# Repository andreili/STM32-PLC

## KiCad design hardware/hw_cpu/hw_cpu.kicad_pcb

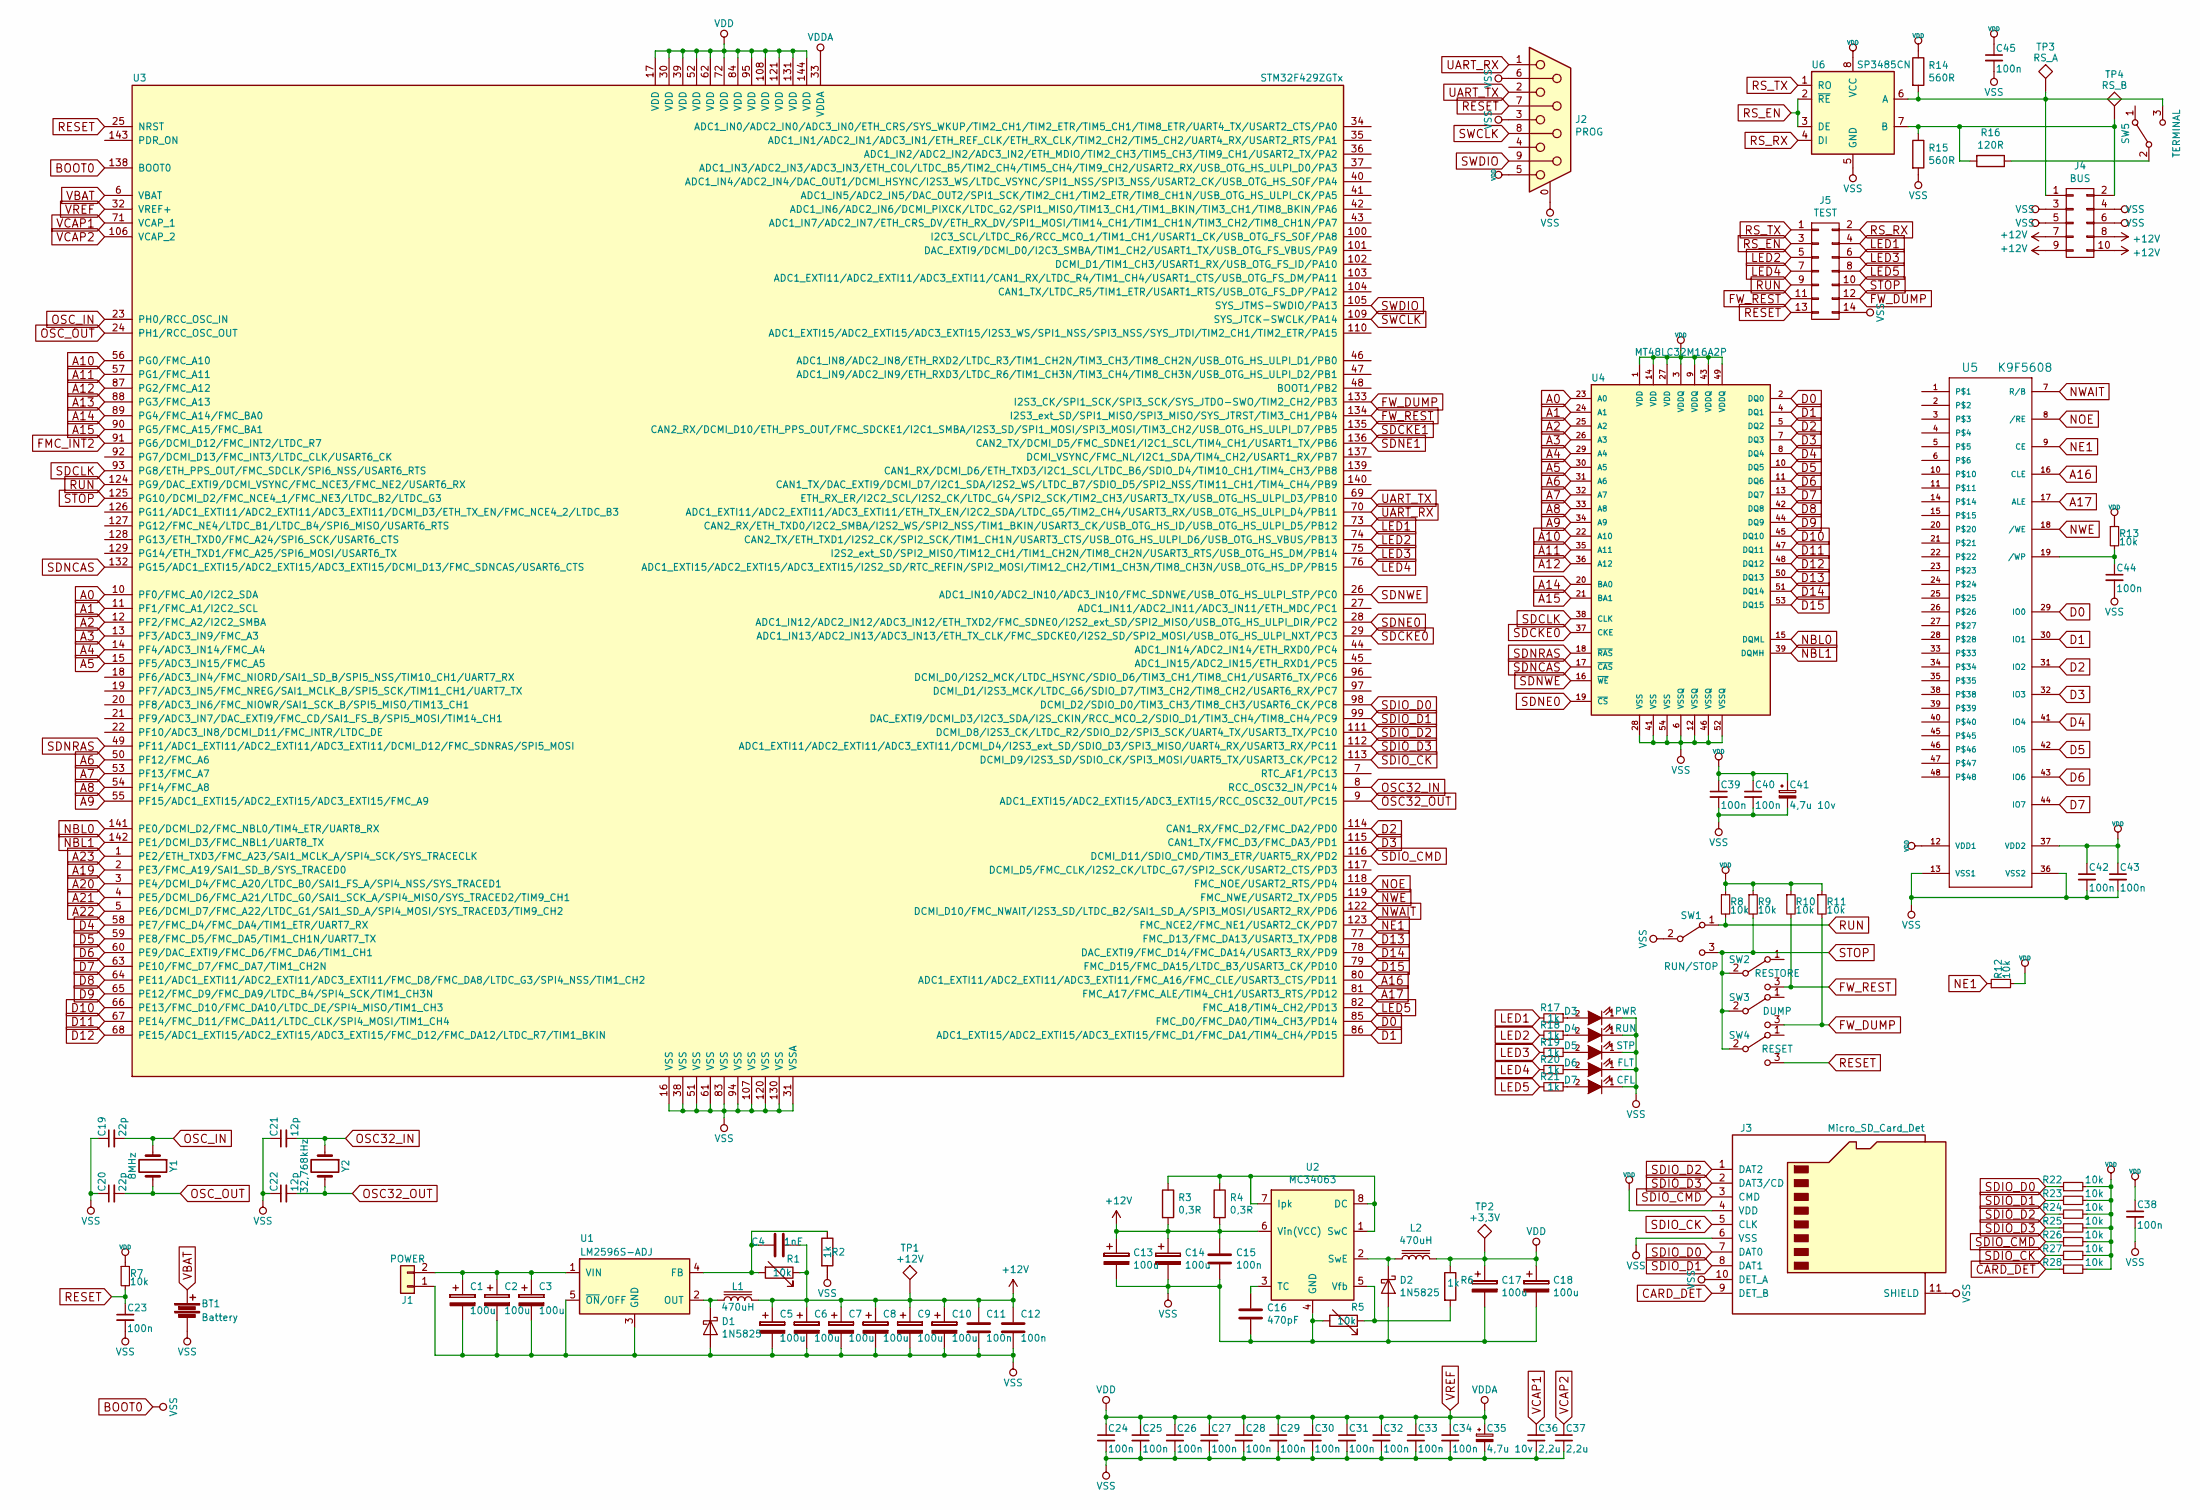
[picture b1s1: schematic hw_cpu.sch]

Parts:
BT1: Battery; keystone_107
C1, C2, C3, C5, C6, C7, C8, C9, C10, C13, C14, C17, C18: 100u; CP_Elec_8x6.5
C4: 1nF; C_0402
C11, C12, C15, C23, C24, C25, C26, C27, C28, C29, C30, C31, C32, C33, C34, C38, C39, C40, C42, C43, C44, C45: 100n; C_0805
C16: 470pF; C_0402
C19, C20: 22p; C_0402
C21, C22: 12p; C_0402
C35: 4,7u 10v; CP_Tantalum_Case-A_EIA-3216-18_Reflow
C36, C37: 2,2u; C_0402
C41: 4,7u 10v; CP_Tantalum_Case-B_EIA-3528-21_Reflow
D1, D2: 1N5825; D_SMA
D3: PWR; LED_0805
D4: RUN; LED_0805
D5: STP; LED_0805
D6: FLT; LED_0805
D7: CFL; LED_0805
J1: POWER; PhoenixContact_MC-G_02x3.81mm_Angled
J2: PROG; DB9FC
J3: Micro_SD_Card_Det; Conn_uSDcard
J4: BUS; he10-10d
J5: TEST; he10-14d
L1, L2: 470uH; Neosid_Inductor_SM-PIC1004H
R1, R5, R7, R8, R9, R10, R11, R12, R13, R22, R23, R24, R25, R26, R27, R28: 10k; R_0805
R2, R6, R17, R18, R19, R20, R21: 1k; R_0805
R3, R4: 0,3R; R_2010
R14, R15: 560R; R_0805
R16: 120R; R_0805
SW1: RUN/STOP; KSA_Tactile_SPST
SW2: RESTORE; SW_SPDT_PCM12
SW3: DUMP; SW_SPDT_PCM12
SW4: RESET; SW_SPDT_PCM12
SW5: TERMINAL; SW_SPDT_PCM12
TP1: +12V; Measurement_Point_Round-TH_Small
TP2: +3,3V; Measurement_Point_Round-TH_Small
TP3: RS_A; Measurement_Point_Round-TH_Small
TP4: RS_B; Measurement_Point_Round-TH_Small
U1: LM2596S-ADJ; TO-263-5_TabPin3
U2: MC34063; SOIC-8_3.9x4.9mm_Pitch1.27mm
U3: STM32F429ZGTx; LQFP-144_20x20mm_Pitch0.5mm
U4: MT48LC32M16A2P; TSOPII-54
U5: K9F5608; TSOP-I-48_12x18.4mm_Pitch0.5mm
U6: SP3485CN; SOIC-8_3.9x4.9mm_Pitch1.27mm
Y1: 8MHz; Crystal_HC49-4H_Vertical
Y2: 32,768kHz; Crystal_Round_d2.0mm_Vertical

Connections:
+12V: C4.2, C5.1, C6.1, C7.1, C8.1, C9.1, C10.1, C11.1, C12.1, C13.1, C14.1, C15.1, J4.7, J4.8, J4.9, J4.10, L1.2, R1.1, R3.2, R4.2, TP1.1, U2.6 (Vin(VCC))
A0: U3.10 (PF0/FMC_A0/I2C2_SDA), U4.23 (A0)
A1: U3.11 (PF1/FMC_A1/I2C2_SCL), U4.24 (A1)
A2: U3.12 (PF2/FMC_A2/I2C2_SMBA), U4.25 (A2)
A3: U3.13 (PF3/ADC3_IN9/FMC_A3), U4.26 (A3)
A4: U3.14 (PF4/ADC3_IN14/FMC_A4), U4.29 (A4)
A5: U3.15 (PF5/ADC3_IN15/FMC_A5), U4.30 (A5)
A6: U3.50 (PF12/FMC_A6), U4.31 (A6)
A7: U3.53 (PF13/FMC_A7), U4.32 (A7)
A8: U3.54 (PF14/FMC_A8), U4.33 (A8)
A9: U3.55 (PF15/ADC1_EXTI15/ADC2_EXTI15/ADC3_EXTI1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), U4.34 (A9)
A10: U3.56 (PG0/FMC_A10), U4.22 (A10)
A11: U3.57 (PG1/FMC_A11), U4.35 (A11)
A12: U3.87 (PG2/FMC_A12), U4.36 (A12)
A13: U3.88 (PG3/FMC_A13)
A14: U3.89 (PG4/FMC_A14/FMC_BA0), U4.20 (BA0)
A15: U3.90 (PG5/FMC_A15/FMC_BA1), U4.21 (BA1)
A16: U3.80 (ADC1_EXTI11/ADC2_EXTI11/ADC3_EXTI11/FMC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), U5.16 (CLE)
A17: U3.81 (FMC_A17/FMC_ALE/TIM4_CH1/USART3_RTS/PD12), U5.17 (ALE)
A19: U3.2 (PE3/FMC_A19/SAI1_SD_B/SYS_TRACED0)
A20: U3.3 (PE4/DCMI_D4/FMC_A20/LTDC_B0/SAI1_FS_A/S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)
A21: U3.4 (PE5/DCMI_D6/FMC_A21/LTDC_G0/SAI1_SCK_A/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)
A22: U3.5 (PE6/DCMI_D7/FMC_A22/LTDC_G1/SAI1_SD_A/S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)
A23: U3.1 (PE2/ETH_TXD3/FMC_A23/SAI1_MCLK_A/SPI4_S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)
BOOT0: BT1.2, C1.2, C2.2, C3.2, C5.2, C6.2, C7.2, C8.2, C9.2, C10.2, C11.2, C12.2, C13.2, C14.2, C15.2, C16.2, C17.2, C18.2, C19.1, C20.1, C21.1, C22.1, C23.2, C24.2, C25.2, C26.2, C27.2, C28.2, C29.2, C30.2, C31.2, C32.2, C33.2, C34.2, C35.2, C36.2, C37.2, C38.2, C39.2, C40.2, C41.2, C42.2, C43.2, C44.2, C45.2, D1.2 (A), D2.2 (A), D3.1 (K), D4.1 (K), D5.1 (K), D6.1 (K), D7.1 (K), J1.1, J2.0 (PAD), J2.3, J2.6, J3.6 (VSS), J3.10 (DET_A), J3.11 (SHIELD), J4.3, J4.4, J4.5, J4.6, J5.14, R2.2, R5.2, R15.2, SW1.2 (B), U1.3 (GND), U1.5 (~ON~/OFF), U2.4 (GND), U3.16 (VSS), U3.31 (VSSA), U3.38 (VSS), U3.51 (VSS), U3.61 (VSS), U3.83 (VSS), U3.94 (VSS), U3.107 (VSS), U3.120 (VSS), U3.130 (VSS), U3.138 (BOOT0), U4.6 (VSSQ), U4.12 (VSSQ), U4.28 (VSS), U4.41 (VSS), U4.46 (VSSQ), U4.52 (VSSQ), U4.54 (VSS), U5.13 (VSS1), U5.36 (VSS2), U6.5 (GND)
CARD_DET: J3.9 (DET_B), R28.1
D0: U3.85 (FMC_D0/FMC_DA0/TIM4_CH3/PD14), U4.2 (DQ0), U5.29 (IO0)
D1: U3.86 (ADC1_EXTI15/ADC2_EXTI15/ADC3_EXTI15/FMC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), U4.4 (DQ1), U5.30 (IO1)
D2: U3.114 (CAN1_RX/FMC_D2/FMC_DA2/PD0), U4.5 (DQ2), U5.31 (IO2)
D3: U3.115 (CAN1_TX/FMC_D3/FMC_DA3/PD1), U4.7 (DQ3), U5.32 (IO3)
D4: U3.58 (PE7/FMC_D4/FMC_DA4/TIM1_ETR/UART7_RX), U4.8 (DQ4), U5.41 (IO4)
D5: U3.59 (PE8/FMC_D5/FMC_DA5/TIM1_CH1N/UART7_TX), U4.10 (DQ5), U5.42 (IO5)
D6: U3.60 (PE9/DAC_EXTI9/FMC_D6/FMC_DA6/TIM1_CH1), U4.11 (DQ6), U5.43 (IO6)
D7: U3.63 (PE10/FMC_D7/FMC_DA7/TIM1_CH2N), U4.13 (DQ7), U5.44 (IO7)
D8: U3.64 (PE11/ADC1_EXTI11/ADC2_EXTI11/ADC3_EXTI1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), U4.42 (DQ8)
D9: U3.65 (PE12/FMC_D9/FMC_DA9/LTDC_B4/SPI4_SCK/TI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), U4.44 (DQ9)
D10: U3.66 (PE13/FMC_D10/FMC_DA10/LTDC_DE/SPI4_MISO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), U4.45 (DQ10)
D11: U3.67 (PE14/FMC_D11/FMC_DA11/LTDC_CLK/SPI4_MOS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), U4.47 (DQ11)
D12: U3.68 (PE15/ADC1_EXTI15/ADC2_EXTI15/ADC3_EXTI1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), U4.48 (DQ12)
D13: U3.77 (FMC_D13/FMC_DA13/USART3_TX/PD8), U4.50 (DQ13)
D14: U3.78 (DAC_EXTI9/FMC_D14/FMC_DA14/USART3_RX/PD9), U4.51 (DQ14)
D15: U3.79 (FMC_D15/FMC_DA15/LTDC_B3/USART3_CK/PD10), U4.53 (DQ15)
FMC_INT2: U3.91 (PG6/DCMI_D12/FMC_INT2/LTDC_R7)
FW_DUMP: J5.12, R11.2, SW3.3 (C), U3.133 (I2S3_CK/SPI1_SCK/SPI3_SCK/SYS_JTDO-SWO/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)
FW_REST: J5.11, R10.2, SW2.3 (C), U3.134 (I2S3_ext_SD/SPI1_MISO/SPI3_MISO/SYS_JTR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)
LED1: J5.4, R17.2, U3.73 (CAN2_RX/ETH_TXD0/I2C2_SMBA/I2S2_WS/SPI2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)
LED2: J5.5, R18.2, U3.74 (CAN2_TX/ETH_TXD1/I2S2_CK/SPI2_SCK/TIM1_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)
LED3: J5.6, R19.2, U3.75 (I2S2_ext_SD/SPI2_MISO/TIM12_CH1/TIM1_CH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)
LED4: J5.7, R20.2, U3.76 (ADC1_EXTI15/ADC2_EXTI15/ADC3_EXTI15/I2S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)
LED5: J5.8, R21.2, U3.82 (FMC_A18/TIM4_CH2/PD13)
NBL0: U3.141 (PE0/DCMI_D2/FMC_NBL0/TIM4_ETR/UART8_RX), U4.15 (DQML)
NBL1: U3.142 (PE1/DCMI_D3/FMC_NBL1/UART8_TX), U4.39 (DQMH)
NE1: R12.1, U3.123 (FMC_NCE2/FMC_NE1/USART2_CK/PD7), U5.9 (CE)
NOE: U3.118 (FMC_NOE/USART2_RTS/PD4), U5.8 (/RE)
NWAIT: U3.122 (DCMI_D10/FMC_NWAIT/I2S3_SD/LTDC_B2/SAI1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), U5.7 (R/B)
NWE: U3.119 (FMC_NWE/USART2_TX/PD5), U5.18 (/WE)
unnamed: C1.1, C2.1, C3.1, J1.2, U1.1 (VIN)
unnamed: C4.1, R1.2, R2.1, U1.4 (FB)
unnamed: C16.1, U2.3 (TC)
unnamed: C44.1, R13.2, U5.19 (/WP)
unnamed: D1.1 (K), L1.1, U1.2 (OUT)
unnamed: D2.1 (K), L2.1, U2.2 (SwE)
unnamed: D3.2 (A), R17.1
unnamed: D4.2 (A), R18.1
unnamed: D5.2 (A), R19.1
unnamed: D6.2 (A), R20.1
unnamed: D7.2 (A), R21.1
unnamed: J4.1, R14.2, SW5.3 (C), TP3.1, U6.6 (A)
unnamed: J4.2, R15.1, R16.2, TP4.1, U6.7 (B)
unnamed: R3.1, R4.1, U2.1 (SwC), U2.7 (Ipk), U2.8 (DC)
unnamed: R5.1, R6.2, U2.5 (Vfb)
unnamed: R16.1, SW5.2 (B)
OSC32_IN: C21.2, U3.8 (RCC_OSC32_IN/PC14), Y2.1
OSC32_OUT: C22.2, U3.9 (ADC1_EXTI15/ADC2_EXTI15/ADC3_EXTI15/RCC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), Y2.2
OSC_IN: C19.2, U3.23 (PH0/RCC_OSC_IN), Y1.1
OSC_OUT: C20.2, U3.24 (PH1/RCC_OSC_OUT), Y1.2
RESET: C23.1, J2.7, J5.13, R7.2, SW4.3 (C), U3.25 (NRST)
RS_EN: J5.3, U6.2 (~RE~), U6.3 (DE)
RS_RX: J5.2, U6.4 (DI)
RS_TX: J5.1, U6.1 (RO)
RUN: J5.9, R8.2, SW1.1 (A), U3.124 (PG9/DAC_EXTI9/DCMI_VSYNC/FMC_NCE3/FMC_N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)
SDCKE0: U3.29 (ADC1_IN13/ADC2_IN13/ADC3_IN13/ETH_TX_CL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), U4.37 (CKE)
SDCKE1: U3.135 (CAN2_RX/DCMI_D10/ETH_PPS_OUT/FMC_SDCKE1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)
SDCLK: U3.93 (PG8/ETH_PPS_OUT/FMC_SDCLK/SPI6_NSS/USAR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), U4.38 (CLK)
SDIO_CK: J3.5 (CLK), R27.1, U3.113 (DCMI_D9/I2S3_SD/SDIO_CK/SPI3_MOSI/UART5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)
SDIO_CMD: J3.3 (CMD), R26.1, U3.116 (DCMI_D11/SDIO_CMD/TIM3_ETR/UART5_RX/PD2)
SDIO_D0: J3.7 (DAT0), R22.1, U3.98 (DCMI_D2/SDIO_D0/TIM3_CH3/TIM8_CH3/USART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)
SDIO_D1: J3.8 (DAT1), R23.1, U3.99 (DAC_EXTI9/DCMI_D3/I2C3_SDA/I2S_CKIN/RCC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)
SDIO_D2: J3.1 (DAT2), R24.1, U3.111 (DCMI_D8/I2S3_CK/LTDC_R2/SDIO_D2/SPI3_SC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)
SDIO_D3: J3.2 (DAT3/CD), R25.1, U3.112 (ADC1_EXTI11/ADC2_EXTI11/ADC3_EXTI11/DCM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)
SDNCAS: U3.132 (PG15/ADC1_EXTI15/ADC2_EXTI15/ADC3_EXTI1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), U4.17 (~CAS~)
SDNE0: U3.28 (ADC1_IN12/ADC2_IN12/ADC3_IN12/ETH_TXD2/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), U4.19 (~CS~)
SDNE1: U3.136 (CAN2_TX/DCMI_D5/FMC_SDNE1/I2C1_SCL/TIM4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)
SDNRAS: U3.49 (PF11/ADC1_EXTI11/ADC2_EXTI11/ADC3_EXTI1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), U4.18 (~RAS~)
SDNWE: U3.26 (ADC1_IN10/ADC2_IN10/ADC3_IN10/FMC_SDNWE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), U4.16 (~WE~)
STOP: J5.10, R9.2, SW1.3 (C), SW2.2 (B), SW3.2 (B), SW4.2 (B), U3.125 (PG10/DCMI_D2/FMC_NCE4_1/FMC_NE3/LTDC_B2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)
SWCLK: J2.8, U3.109 (SYS_JTCK-SWCLK/PA14)
SWDIO: J2.9, U3.105 (SYS_JTMS-SWDIO/PA13)
UART_RX: J2.1, U3.70 (ADC1_EXTI11/ADC2_EXTI11/ADC3_EXTI11/ETH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)
UART_TX: J2.2, U3.69 (ETH_RX_ER/I2C2_SCL/I2S2_CK/LTDC_G4/SPI2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)
VBAT: BT1.1, U3.6 (VBAT)
VCAP1: C36.1, U3.71 (VCAP_1)
VCAP2: C37.1, U3.106 (VCAP_2)
VREF: C17.1, C18.1, C24.1, C25.1, C26.1, C27.1, C28.1, C29.1, C30.1, C31.1, C32.1, C33.1, C34.1, C35.1, C38.1, C39.1, C40.1, C41.1, C42.1, C43.1, C45.1, J2.5, J3.4 (VDD), L2.2, R6.1, R7.1, R8.1, R9.1, R10.1, R11.1, R12.2, R13.1, R14.1, R22.2, R23.2, R24.2, R25.2, R26.2, R27.2, R28.2, TP2.1, U3.17 (VDD), U3.30 (VDD), U3.32 (VREF+), U3.33 (VDDA), U3.39 (VDD), U3.52 (VDD), U3.62 (VDD), U3.72 (VDD), U3.84 (VDD), U3.95 (VDD), U3.108 (VDD), U3.121 (VDD), U3.131 (VDD), U3.144 (VDD), U4.1 (VDD), U4.3 (VDDQ), U4.9 (VDDQ), U4.14 (VDD), U4.27 (VDD), U4.43 (VDDQ), U4.49 (VDDQ), U5.12 (VDD1), U5.37 (VDD2), U6.8 (VCC)

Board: 2 copper layers, 104 parts (2 on the bottom side), 91 nets, no tracks yet.

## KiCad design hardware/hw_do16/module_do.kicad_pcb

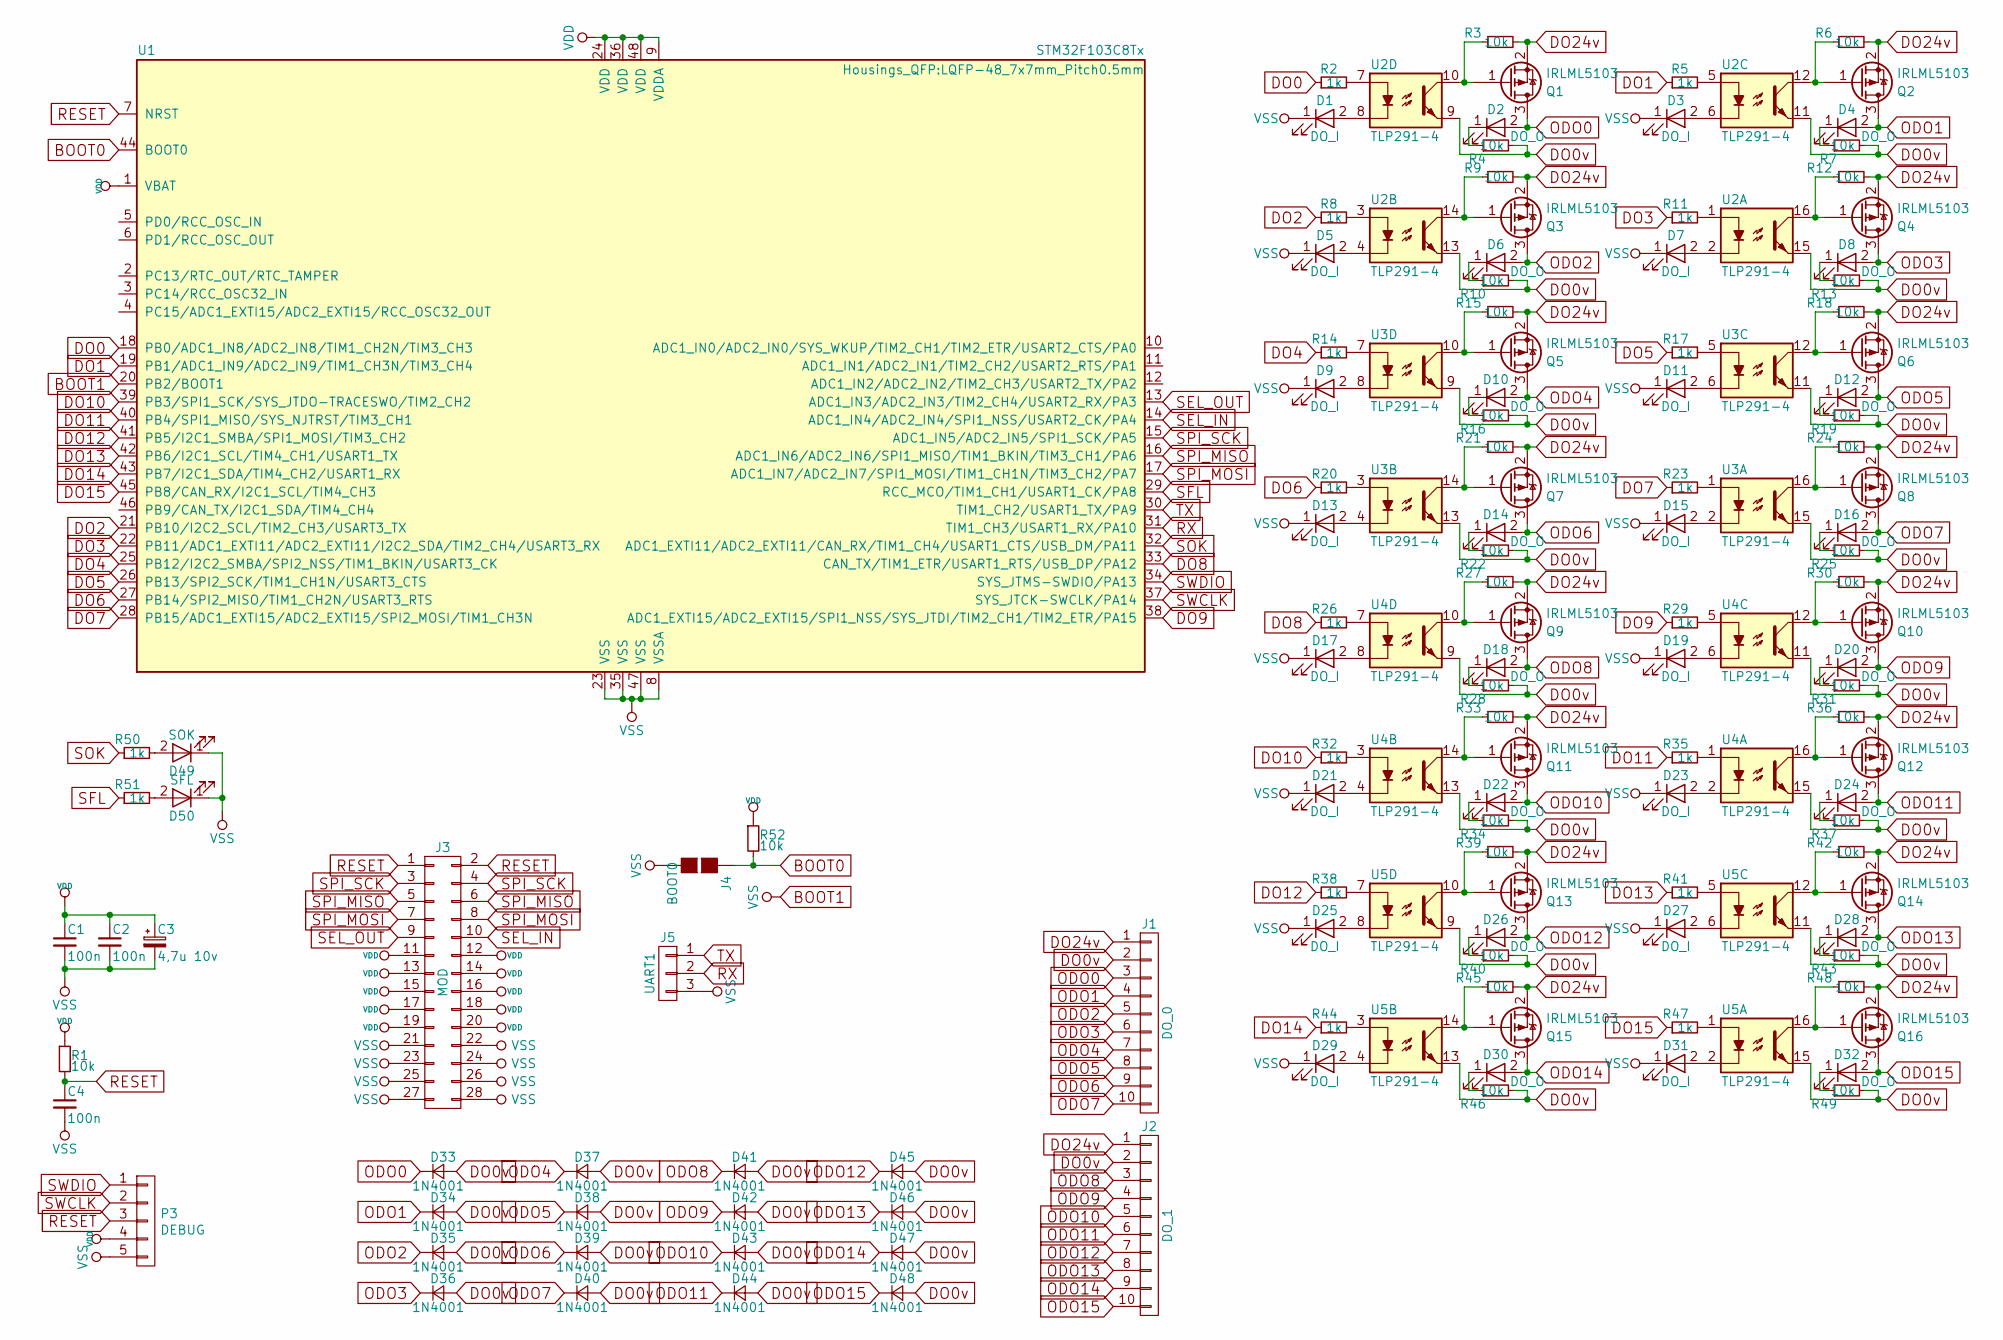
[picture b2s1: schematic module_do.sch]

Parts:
C1, C2, C4: 100n; C_0805
C3: 4,7u 10v; CP_Tantalum_Case-A_EIA-3216-18_Wave
D1, D3, D5, D7, D9, D11, D13, D15, D17, D19, D21, D23, D25, D27, D29, D31: DO_I; LED_0603
D2, D4, D6, D8, D10, D12, D14, D16, D18, D20, D22, D24, D26, D28, D30, D32: DO_O; LED_0603
D33, D34, D35, D36, D37, D38, D39, D40, D41, D42, D43, D44, D45, D46, D47, D48: 1N4001; D_SOD-123
D49: SOK; LED_0603
D50: SFL; LED_0603
J1: DO_0; PhoenixContact_MC-G_10x3.81mm_Angled
J2: DO_1; PhoenixContact_MC-G_10x3.81mm_Angled
J3: MOD; Pin_Header_2.00mm_SMD
J4: BOOT0; GS2
J5: UART1; Pin_Header_Straight_1x03_Pitch2.00mm
P3: DEBUG; Socket_Strip_Straight_1x05_Pitch2.00mm
Q1, Q2, Q3, Q4, Q5, Q6, Q7, Q8, Q9, Q10, Q11, Q12, Q13, Q14, Q15, Q16: IRLML5103; SOT-23
R1, R3, R4, R6, R7, R9, R10, R12, R13, R15, R16, R18, R19, R21, R22, R24, R25, R27, R28, R30, R31, R33, R34, R36, R37, R39, R40, R42, R43, R45, R46, R48, R49, R52: 10k; R_0805
R2, R5, R8, R11, R14, R17, R20, R23, R26, R29, R32, R35, R38, R41, R44, R47, R50, R51: 1k; R_0805
U1: STM32F103C8Tx; LQFP-48_7x7mm_Pitch0.5mm
U2, U3, U4, U5: TLP291-4; SO-16-N

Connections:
BOOT0: J4.1 (G1), R52.2, U1.44 (BOOT0)
BOOT1: C1.2, C2.2, C3.2, C4.2, D1.1 (K), D3.1 (K), D5.1 (K), D7.1 (K), D9.1 (K), D11.1 (K), D13.1 (K), D15.1 (K), D17.1 (K), D19.1 (K), D21.1 (K), D23.1 (K), D25.1 (K), D27.1 (K), D29.1 (K), D31.1 (K), D49.1 (K), D50.1 (K), J3.21, J3.22, J3.23, J3.24, J3.25, J3.26, J3.27, J3.28, J4.2 (G2), J5.3, P3.5, U1.8 (VSSA), U1.20 (PB2/BOOT1), U1.23 (VSS), U1.35 (VSS), U1.47 (VSS)
DO0: R2.1, U1.18 (PB0/ADC1_IN8/ADC2_IN8/TIM1_CH2N/TIM3_CH3)
DO0v: D33.2 (A), D34.2 (A), D35.2 (A), D36.2 (A), D37.2 (A), D38.2 (A), D39.2 (A), D40.2 (A), D41.2 (A), D42.2 (A), D43.2 (A), D44.2 (A), D45.2 (A), D46.2 (A), D47.2 (A), D48.2 (A), J1.2, J2.2, R4.2, R7.2, R10.2, R13.2, R16.2, R19.2, R22.2, R25.2, R28.2, R31.2, R34.2, R37.2, R40.2, R43.2, R46.2, R49.2, U2.9, U2.11, U2.13, U2.15, U3.9, U3.11, U3.13, U3.15, U4.9, U4.11, U4.13, U4.15, U5.9, U5.11, U5.13, U5.15
DO1: R5.1, U1.19 (PB1/ADC1_IN9/ADC2_IN9/TIM1_CH3N/TIM3_CH4)
DO2: R8.1, U1.21 (PB10/I2C2_SCL/TIM2_CH3/USART3_TX)
DO3: R11.1, U1.22 (PB11/ADC1_EXTI11/ADC2_EXTI11/I2C2_SDA/T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)
DO4: R14.1, U1.25 (PB12/I2C2_SMBA/SPI2_NSS/TIM1_BKIN/USART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)
DO5: R17.1, U1.26 (PB13/SPI2_SCK/TIM1_CH1N/USART3_CTS)
DO6: R20.1, U1.27 (PB14/SPI2_MISO/TIM1_CH2N/USART3_RTS)
DO7: R23.1, U1.28 (PB15/ADC1_EXTI15/ADC2_EXTI15/SPI2_MOSI/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)
DO8: R26.1, U1.33 (CAN_TX/TIM1_ETR/USART1_RTS/USB_DP/PA12)
DO9: R29.1, U1.38 (ADC1_EXTI15/ADC2_EXTI15/SPI1_NSS/SYS_JT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)
DO10: R32.1, U1.39 (PB3/SPI1_SCK/SYS_JTDO-TRACESWO/TIM2_CH2)
DO11: R35.1, U1.40 (PB4/SPI1_MISO/SYS_NJTRST/TIM3_CH1)
DO12: R38.1, U1.41 (PB5/I2C1_SMBA/SPI1_MOSI/TIM3_CH2)
DO13: R41.1, U1.42 (PB6/I2C1_SCL/TIM4_CH1/USART1_TX)
DO14: R44.1, U1.43 (PB7/I2C1_SDA/TIM4_CH2/USART1_RX)
DO15: R47.1, U1.45 (PB8/CAN_RX/I2C1_SCL/TIM4_CH3)
DO24v: J1.1, J2.1, Q1.2 (S), Q2.2 (S), Q3.2 (S), Q4.2 (S), Q5.2 (S), Q6.2 (S), Q7.2 (S), Q8.2 (S), Q9.2 (S), Q10.2 (S), Q11.2 (S), Q12.2 (S), Q13.2 (S), Q14.2 (S), Q15.2 (S), Q16.2 (S), R3.2, R6.2, R9.2, R12.2, R15.2, R18.2, R21.2, R24.2, R27.2, R30.2, R33.2, R36.2, R39.2, R42.2, R45.2, R48.2
unnamed: D1.2 (A), U2.8
unnamed: D2.1 (K), R4.1
unnamed: D3.2 (A), U2.6
unnamed: D4.1 (K), R7.1
unnamed: D5.2 (A), U2.4
unnamed: D6.1 (K), R10.1
unnamed: D7.2 (A), U2.2
unnamed: D8.1 (K), R13.1
unnamed: D9.2 (A), U3.8
unnamed: D10.1 (K), R16.1
unnamed: D11.2 (A), U3.6
unnamed: D12.1 (K), R19.1
unnamed: D13.2 (A), U3.4
unnamed: D14.1 (K), R22.1
unnamed: D15.2 (A), U3.2
unnamed: D16.1 (K), R25.1
unnamed: D17.2 (A), U4.8
unnamed: D18.1 (K), R28.1
unnamed: D19.2 (A), U4.6
unnamed: D20.1 (K), R31.1
unnamed: D21.2 (A), U4.4
unnamed: D22.1 (K), R34.1
unnamed: D23.2 (A), U4.2
unnamed: D24.1 (K), R37.1
unnamed: D25.2 (A), U5.8
unnamed: D26.1 (K), R40.1
unnamed: D27.2 (A), U5.6
unnamed: D28.1 (K), R43.1
unnamed: D29.2 (A), U5.4
unnamed: D30.1 (K), R46.1
unnamed: D31.2 (A), U5.2
unnamed: D32.1 (K), R49.1
unnamed: D49.2 (A), R50.2
unnamed: D50.2 (A), R51.2
unnamed: Q1.1 (G), R3.1, U2.10
unnamed: Q2.1 (G), R6.1, U2.12
unnamed: Q3.1 (G), R9.1, U2.14
unnamed: Q4.1 (G), R12.1, U2.16
unnamed: Q5.1 (G), R15.1, U3.10
unnamed: Q6.1 (G), R18.1, U3.12
unnamed: Q7.1 (G), R21.1, U3.14
unnamed: Q8.1 (G), R24.1, U3.16
unnamed: Q9.1 (G), R27.1, U4.10
unnamed: Q10.1 (G), R30.1, U4.12
unnamed: Q11.1 (G), R33.1, U4.14
unnamed: Q12.1 (G), R36.1, U4.16
unnamed: Q13.1 (G), R39.1, U5.10
unnamed: Q14.1 (G), R42.1, U5.12
unnamed: Q15.1 (G), R45.1, U5.14
unnamed: Q16.1 (G), R48.1, U5.16
unnamed: R2.2, U2.7
unnamed: R5.2, U2.5
unnamed: R8.2, U2.3
unnamed: R11.2, U2.1
unnamed: R14.2, U3.7
unnamed: R17.2, U3.5
unnamed: R20.2, U3.3
unnamed: R23.2, U3.1
unnamed: R26.2, U4.7
unnamed: R29.2, U4.5
unnamed: R32.2, U4.3
unnamed: R35.2, U4.1
unnamed: R38.2, U5.7
unnamed: R41.2, U5.5
unnamed: R44.2, U5.3
unnamed: R47.2, U5.1
ODO0: D2.2 (A), D33.1 (K), J1.3, Q1.3 (D)
ODO1: D4.2 (A), D34.1 (K), J1.4, Q2.3 (D)
ODO2: D6.2 (A), D35.1 (K), J1.5, Q3.3 (D)
ODO3: D8.2 (A), D36.1 (K), J1.6, Q4.3 (D)
ODO4: D10.2 (A), D37.1 (K), J1.7, Q5.3 (D)
ODO5: D12.2 (A), D38.1 (K), J1.8, Q6.3 (D)
ODO6: D14.2 (A), D39.1 (K), J1.9, Q7.3 (D)
ODO7: D16.2 (A), D40.1 (K), J1.10, Q8.3 (D)
ODO8: D18.2 (A), D41.1 (K), J2.3, Q9.3 (D)
ODO9: D20.2 (A), D42.1 (K), J2.4, Q10.3 (D)
ODO10: D22.2 (A), D43.1 (K), J2.5, Q11.3 (D)
ODO11: D24.2 (A), D44.1 (K), J2.6, Q12.3 (D)
ODO12: D26.2 (A), D45.1 (K), J2.7, Q13.3 (D)
ODO13: D28.2 (A), D46.1 (K), J2.8, Q14.3 (D)
ODO14: D30.2 (A), D47.1 (K), J2.9, Q15.3 (D)
ODO15: D32.2 (A), D48.1 (K), J2.10, Q16.3 (D)
RESET: C4.1, J3.1, J3.2, P3.3, R1.2, U1.7 (NRST)
RX: J5.2, U1.31 (TIM1_CH3/USART1_RX/PA10)
SEL_IN: J3.10, U1.14 (ADC1_IN4/ADC2_IN4/SPI1_NSS/USART2_CK/PA4)
SEL_OUT: J3.9, U1.13 (ADC1_IN3/ADC2_IN3/TIM2_CH4/USART2_RX/PA3)
SFL: R51.1, U1.29 (RCC_MCO/TIM1_CH1/USART1_CK/PA8)
SOK: R50.1, U1.32 (ADC1_EXTI11/ADC2_EXTI11/CAN_RX/TIM1_CH4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)
SPI_MISO: J3.5, J3.6, U1.16 (ADC1_IN6/ADC2_IN6/SPI1_MISO/TIM1_BKIN/T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)
SPI_MOSI: J3.7, J3.8, U1.17 (ADC1_IN7/ADC2_IN7/SPI1_MOSI/TIM1_CH1N/T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)
SPI_SCK: J3.3, J3.4, U1.15 (ADC1_IN5/ADC2_IN5/SPI1_SCK/PA5)
SWCLK: P3.2, U1.37 (SYS_JTCK-SWCLK/PA14)
SWDIO: P3.1, U1.34 (SYS_JTMS-SWDIO/PA13)
TX: J5.1, U1.30 (TIM1_CH2/USART1_TX/PA9)
VDD: C1.1, C2.1, C3.1, J3.11, J3.12, J3.13, J3.14, J3.15, J3.16, J3.17, J3.18, J3.19, J3.20, P3.4, R1.1, R52.1, U1.1 (VBAT), U1.9 (VDDA), U1.24 (VDD), U1.36 (VDD), U1.48 (VDD)

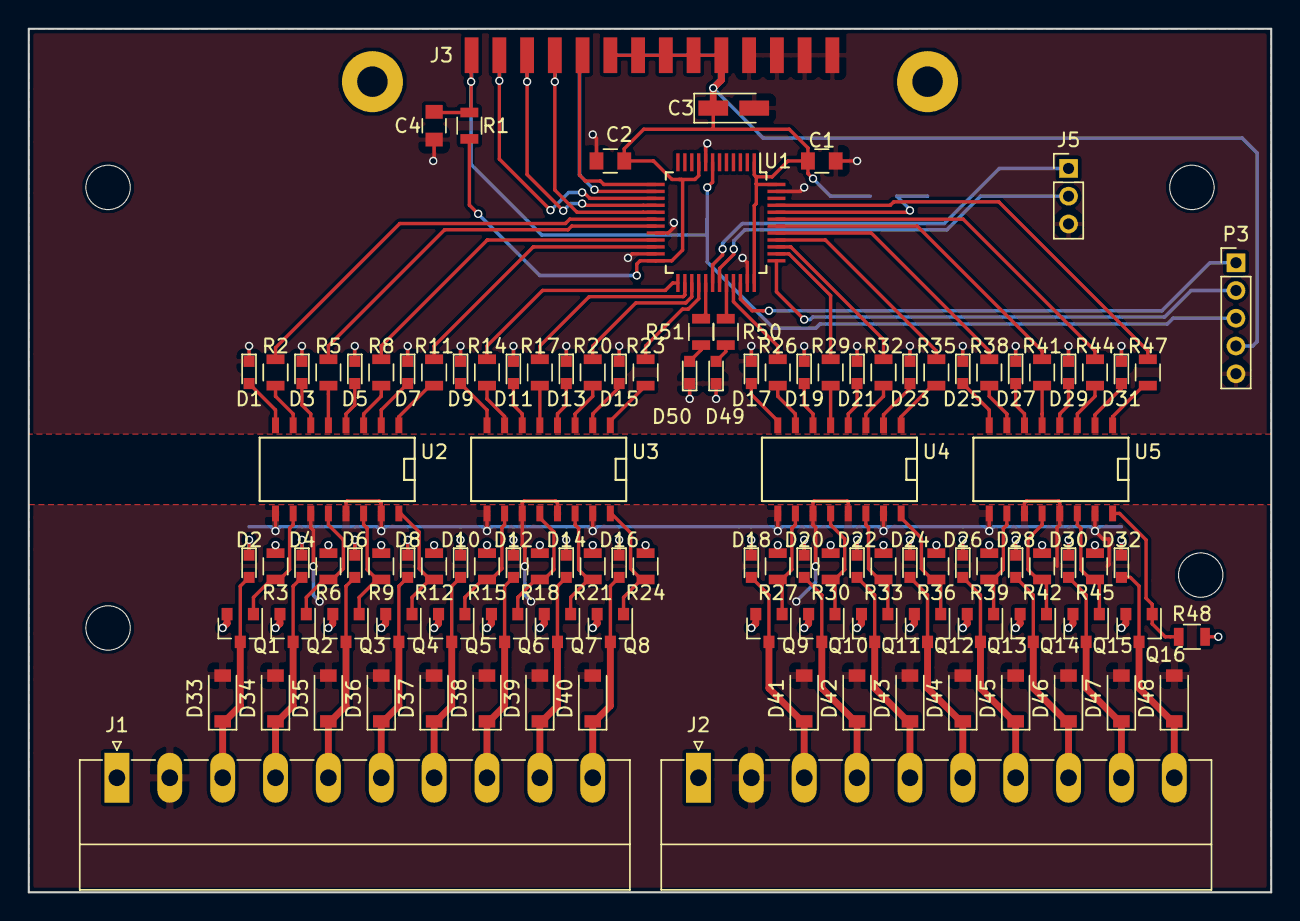
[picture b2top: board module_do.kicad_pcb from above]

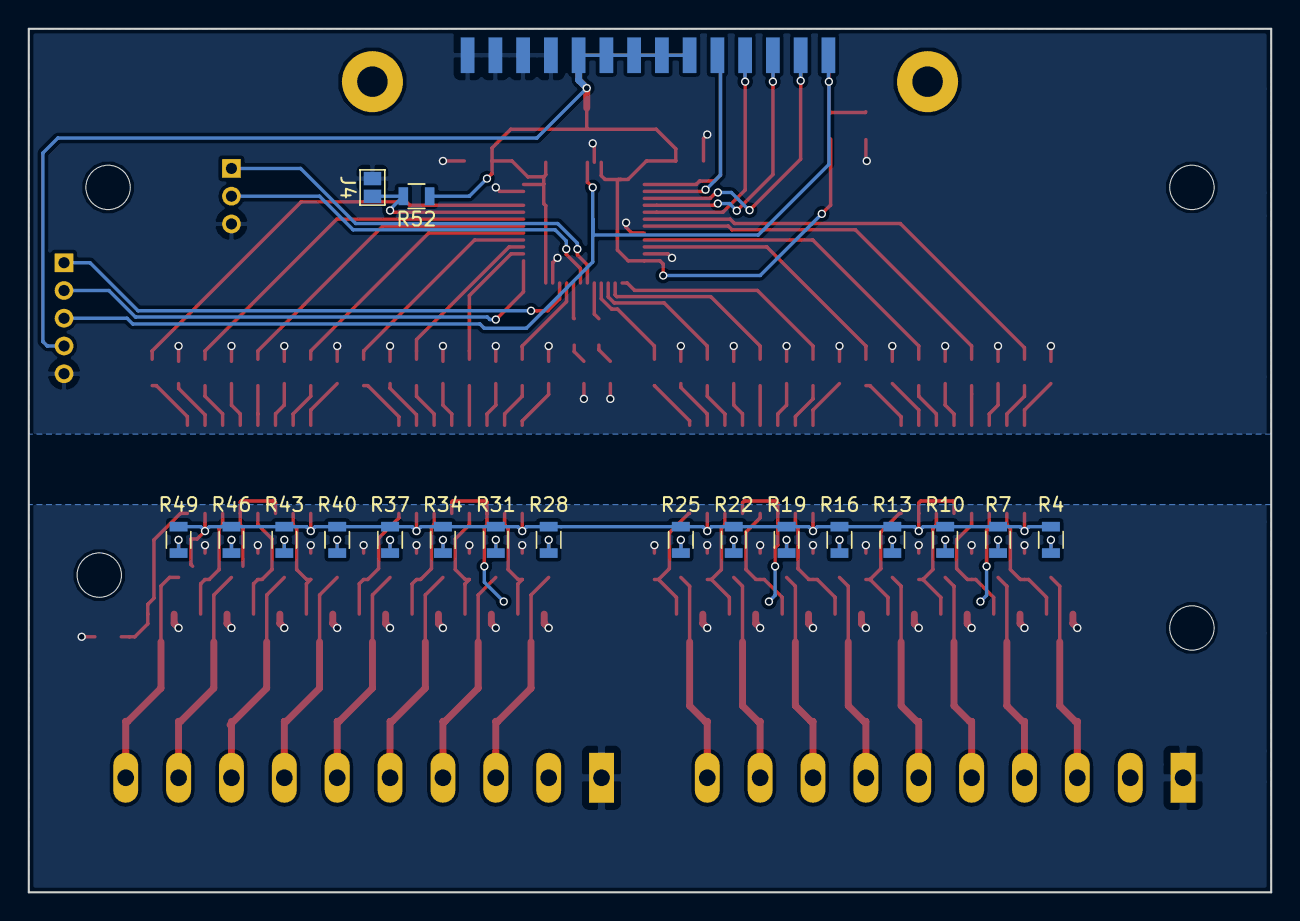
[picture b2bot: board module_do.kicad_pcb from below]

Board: 2 copper layers, 89.5 x 62.2 mm, 133 parts (18 on the bottom side), 115 nets.
